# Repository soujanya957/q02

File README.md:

# q02

Split wireless keyboard with encoders.

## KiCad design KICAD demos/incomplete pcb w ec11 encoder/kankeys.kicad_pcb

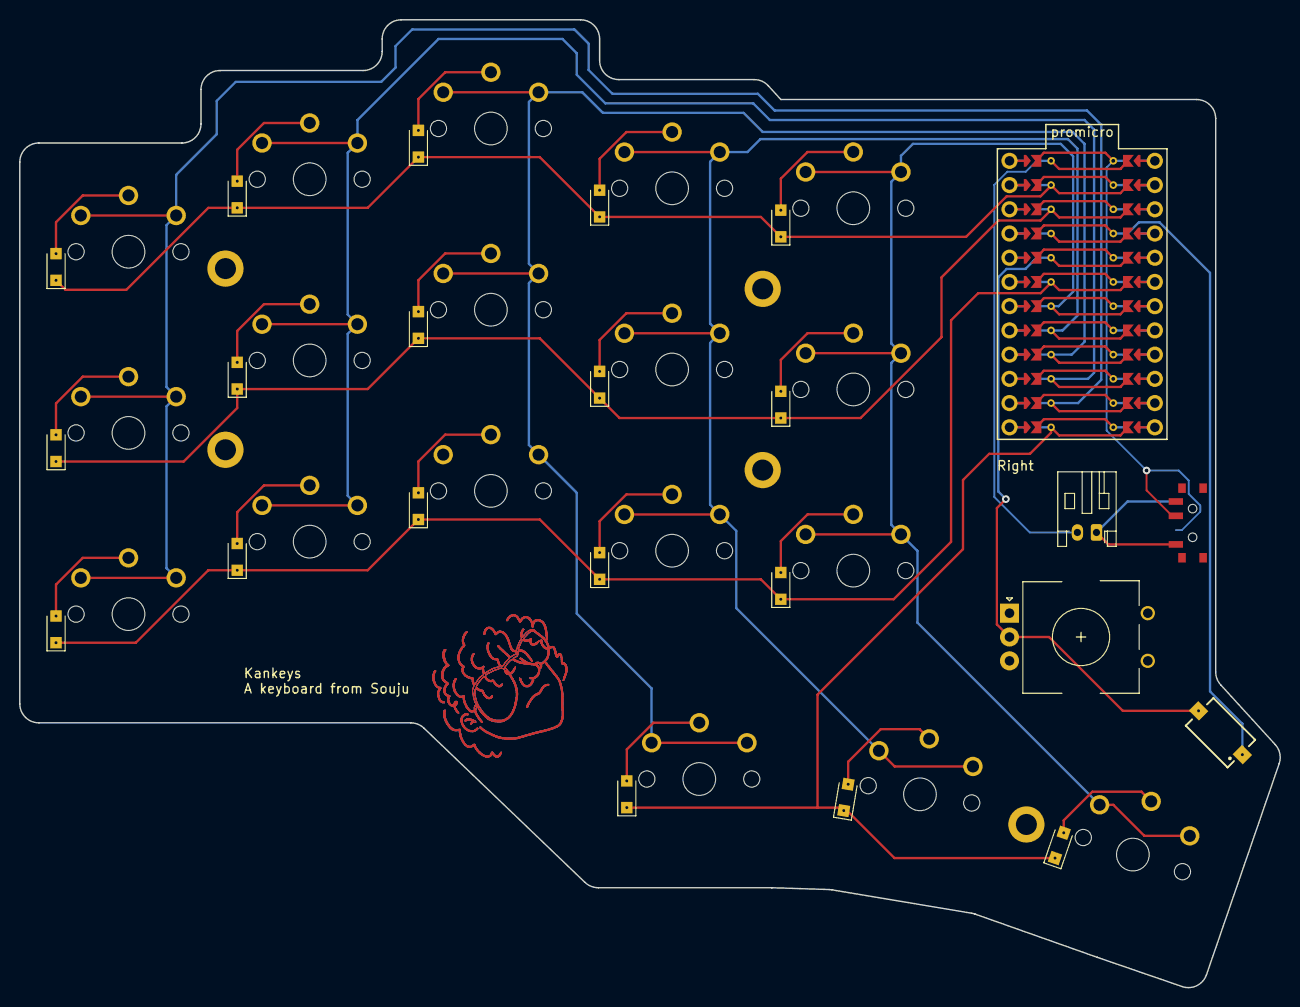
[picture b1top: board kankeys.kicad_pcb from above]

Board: 2 copper layers, 132.2 x 101.5 mm, 45 parts (0 on the bottom side), 11 nets.

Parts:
D1, D2, D3, D4, D5, D6, D7, D8, D9, D10, D11, D12, D13, D14, D15, D16, D17, D18: Nexperia_CFP3_SOD-123W
H1, H2, H3, H4, H5: mounting_hole
S1, S2, S3, S4, S5, S6, S7, S8, S9, S10, S11, S12, S13, S14, S15, S16, S17, S18: PG1350
S19: 434121025816
T1: SW_SPDT_PCM12
_2: rotary_encoder
_3: JST_PH_S2B-PH-K_1x02_P2.00mm_Horizontal

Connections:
GND: S19.2, _2.C
P0: D2.1, D2.2, D5.1, D5.2, D8.1, D8.2, D11.1, D11.2, D14.1, D14.2, S2.2, S5.2, S8.2, S11.2, S14.2
P1: D3.1, D3.2, D6.1, D6.2, D9.1, D9.2, D12.1, D12.2, D15.1, D15.2, S3.2, S6.2, S9.2, S12.2, S15.2
P2: D1.1, D1.2, D4.1, D4.2, D7.1, D7.2, D10.1, D10.2, D13.1, D13.2, S1.2, S4.2, S7.2, S10.2, S13.2
P3: S13.1, S14.1, S15.1, S18.1
P4: S10.1, S11.1, S12.1, S17.1
P5: S7.1, S8.1, S9.1, S16.1
P6: S4.1, S5.1, S6.1
P7: S1.1, S2.1, S3.1
P8: D16.1, D16.2, D17.1, D17.2, D18.1, D18.2, S16.2, S17.2, S18.2
pos: T1.1, _3.1

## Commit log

2024-08-17 Push Prototype 1.0
2024-08-17 Images
